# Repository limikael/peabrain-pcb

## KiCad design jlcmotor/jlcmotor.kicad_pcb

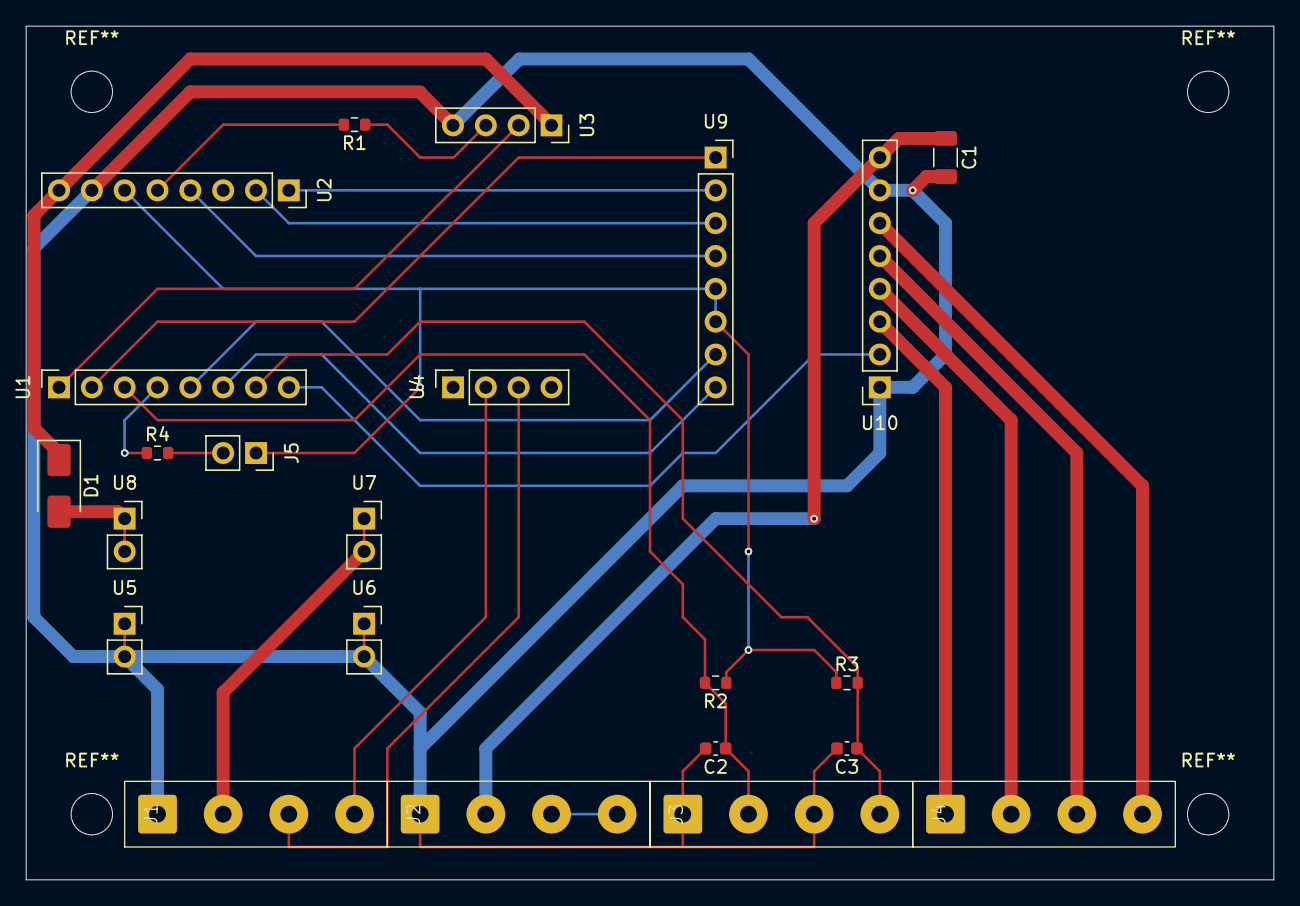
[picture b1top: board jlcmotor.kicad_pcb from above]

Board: 2 copper layers, 96.5 x 66.0 mm, 23 parts (0 on the bottom side), 26 nets.

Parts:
C1: C_1206_3216Metric
C2, C3: C_0603_1608Metric
D1: D_SMA
J1: ScrewTerminal; ScrewTerminals_4P
J2, J3, J4: ScrewTerminals_4P
J5: PinSocket_1x02_P2.54mm_Vertical
R1, R2, R3, R4: R_0603_1608Metric
U1, U2: PinHeader8; PinSocket_1x08_P2.54mm_Vertical
U3, U4: PinSocket_1x04_P2.54mm_Vertical
U5, U6, U7, U8: PinSocket_1x02_P2.54mm_Vertical
U9, U10: PinSocket_1x08_P2.54mm_Vertical

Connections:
/3V3: J5.1, R2.1, R3.1, U2.6, U9.5, U9.6
/5V: D1.1 (K), U2.8, U3.1
/12V: J1.2, U7.1, U7.2
/CANH: J1.3, U4.3
/CANL: J1.4, U4.2
/GND: C1.2, C2.2, C3.2, J1.1, J2.1, J3.1, J3.3, U2.7, U3.4, U5.1, U5.2, U6.1, U6.2, U10.1, U10.7
/VMOT: C1.1, J2.2, U10.8
unnamed: D1.2 (A), U8.1, U8.2
unnamed: C2.1, J3.2, R2.2, U1.3
unnamed: C3.1, J3.4, R3.2, U1.7
unnamed: J4.1, U10.3
unnamed: J4.2, U10.4
unnamed: J4.3, U10.5
unnamed: J4.4, U10.6
unnamed: J5.2, R4.2
unnamed: U1.1, U3.2
unnamed: U1.2, U9.1
unnamed: R4.1, U1.4
unnamed: U1.5, U9.7
unnamed: U1.6, U9.8
unnamed: U1.8, U10.2
unnamed: U2.1, U9.2
unnamed: U2.2, U9.3
unnamed: U2.4, U9.4
unnamed: R1.2, U2.5
unnamed: R1.1, U3.3

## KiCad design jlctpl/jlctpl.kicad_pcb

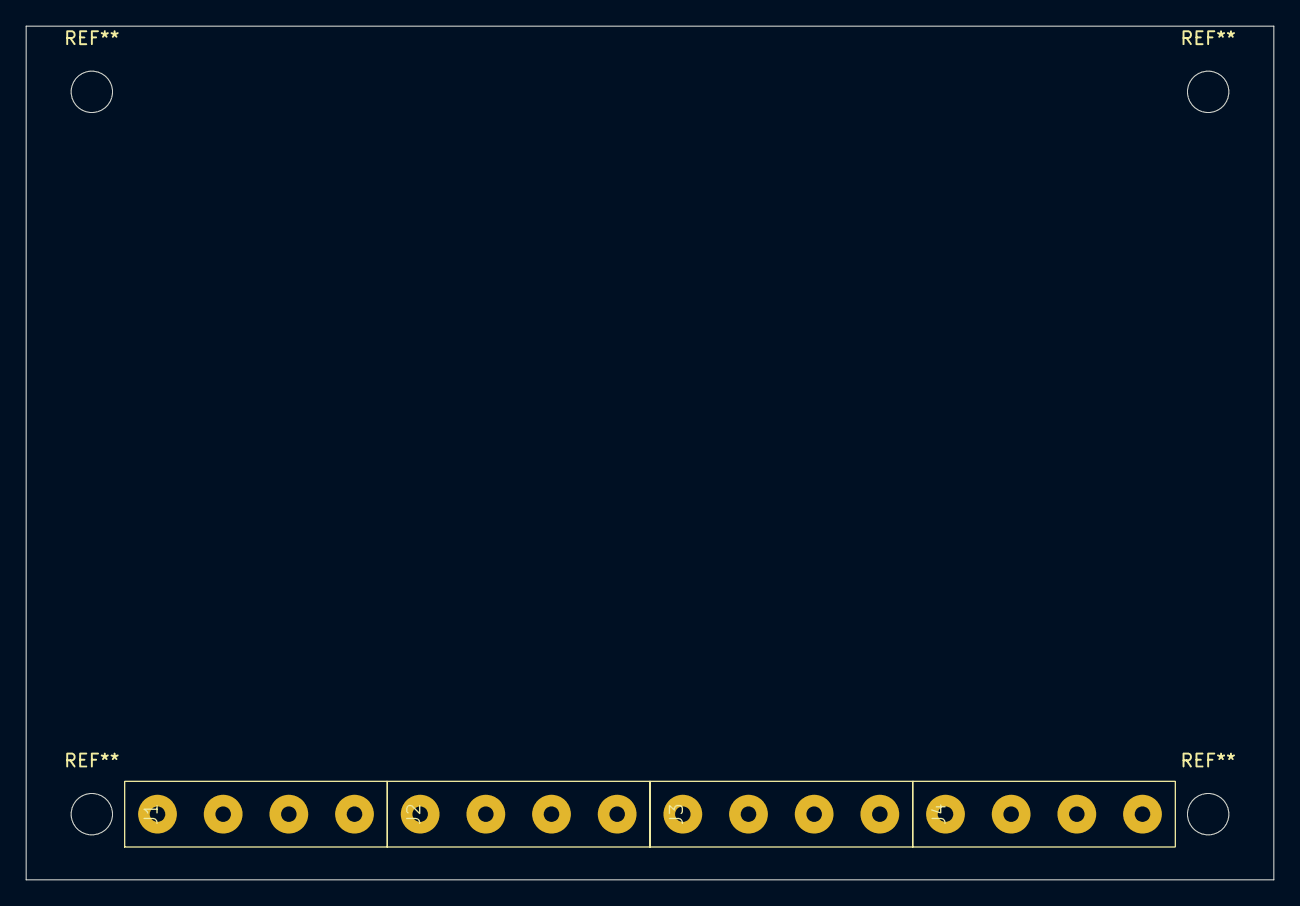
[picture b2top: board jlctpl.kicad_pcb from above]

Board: 2 copper layers, 96.5 x 66.0 mm, 4 parts (0 on the bottom side), 2 nets, no tracks yet.

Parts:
J1, J3, J4: Screw Termial; ScrewTerminals_4P
J2: Screw Terminal; ScrewTerminals_4P

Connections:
/3V3: J2.2, J3.2
/GND: J1.1, J2.1, J3.1

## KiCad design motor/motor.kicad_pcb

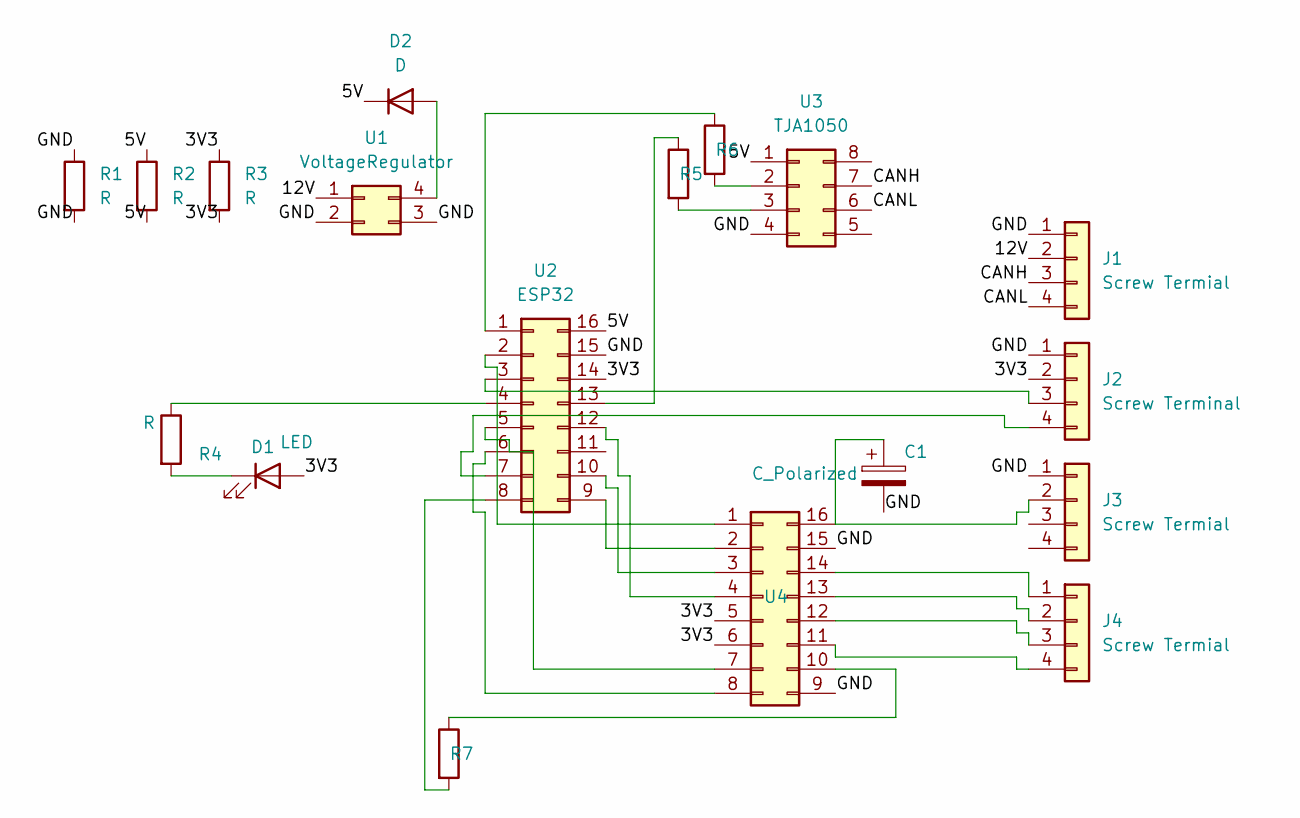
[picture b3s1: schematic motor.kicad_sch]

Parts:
C1: C_Polarized; PinHeader_1x02_P2.54mm_Vertical
D1: LED; PinHeader_Diode
D2: D; R_Axial_DIN0207_L6.3mm_D2.5mm_P10.16mm_Horizontal
J1, J3, J4: Screw Termial; ScrewTerminals_4P
J2: Screw Terminal; ScrewTerminals_4P
R1, R2, R3, R4: R; R_Axial_DIN0207_L6.3mm_D2.5mm_P10.16mm_Horizontal
R5, R6: R_Axial_DIN0207_L6.3mm_D2.5mm_P10.16mm_Horizontal
R7: R_Axial_DIN0207_L6.3mm_D2.5mm_P10.16mm_Horizontal
U1: VoltageRegulator
U2: ESP32
U3: TJA1050
U4: DRV8825

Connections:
/3V3: D1.2 (A), J2.2, R3.1, R3.2, U2.14, U4.5, U4.6
/5V: D2.1 (K), R2.1, R2.2, U2.16, U3.1
/12V: J1.2, U1.1
/CANH: J1.3, U3.7
/CANL: J1.4, U3.6
/GND: C1.2, J1.1, J2.1, J3.1, R1.1, R1.2, U1.2, U1.3, U2.15, U3.4, U4.9, U4.15
unnamed: D1.1 (K), R4.2
unnamed: D2.2 (A), U1.4
unnamed: J2.3, U2.3
unnamed: J2.4, U2.7
unnamed: C1.1, J3.2, U4.16
unnamed: J4.1, U4.14
unnamed: J4.2, U4.13
unnamed: J4.3, U4.12
unnamed: J4.4, U4.11
unnamed: R6.1, U2.1
unnamed: U2.2, U4.1
unnamed: R4.1, U2.4
unnamed: U2.5, U4.7
unnamed: U2.6, U4.8
unnamed: R7.2, U2.8
unnamed: U2.9, U4.2
unnamed: U2.10, U4.3
unnamed: U2.12, U4.4
unnamed: R5.1, U2.13
unnamed: R6.2, U3.2
unnamed: R5.2, U3.3
unnamed: R7.1, U4.10

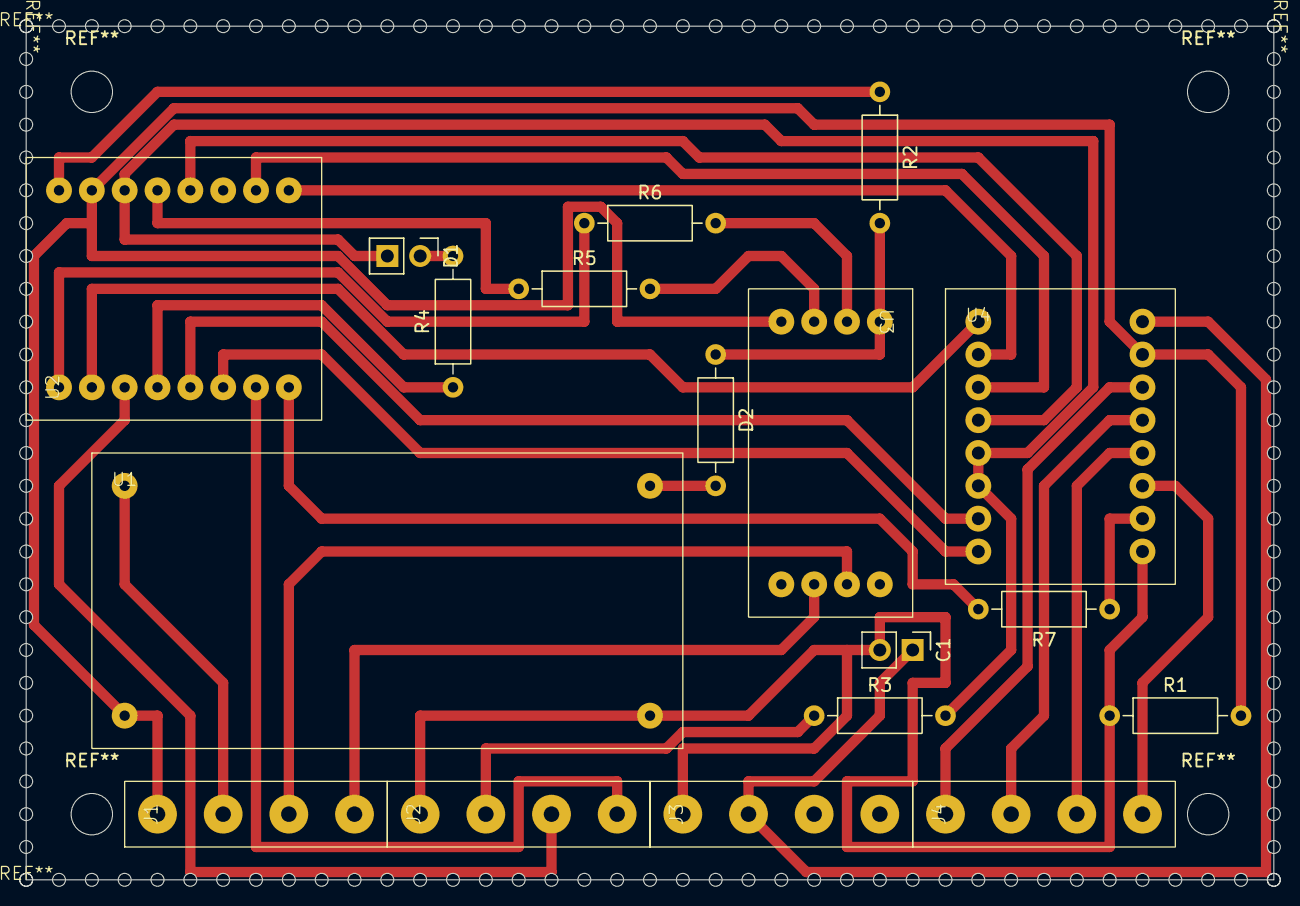
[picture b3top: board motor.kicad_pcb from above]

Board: 2 copper layers, 96.5 x 66.0 mm, 18 parts (0 on the bottom side), 28 nets.

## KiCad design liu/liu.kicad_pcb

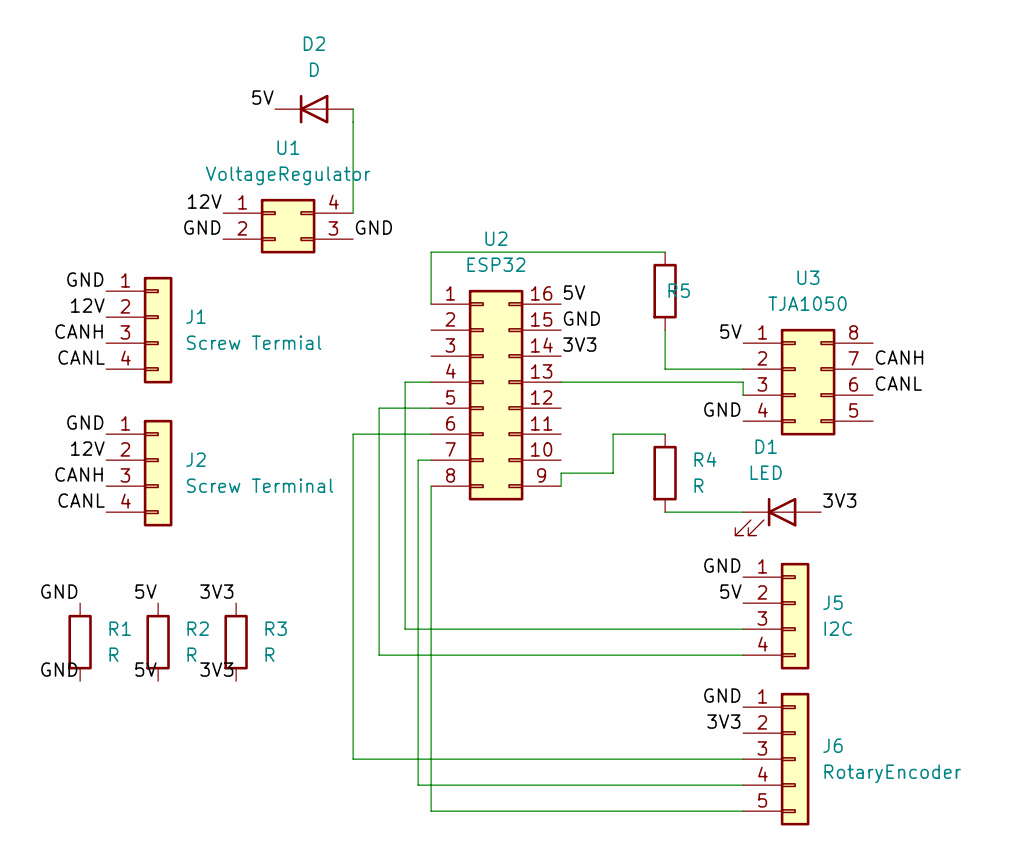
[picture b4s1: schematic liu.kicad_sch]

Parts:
D1: LED; PinHeader_1x02_P2.54mm_Vertical
D2: D; R_Axial_DIN0207_L6.3mm_D2.5mm_P10.16mm_Horizontal
J1: Screw Termial; ScrewTerminals_4P
J2: Screw Terminal; ScrewTerminals_4P
J5: I2C; I2C_Connector
J6: RotaryEncoder; RotaryEncoderConnection
R1, R2, R3, R4: R; R_Axial_DIN0207_L6.3mm_D2.5mm_P10.16mm_Horizontal
R5: R_Axial_DIN0207_L6.3mm_D2.5mm_P10.16mm_Horizontal
U1: VoltageRegulator
U2: ESP32
U3: TJA1050

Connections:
/3V3: D1.2 (A), J6.2, R3.1, R3.2, U2.14
/5V: D2.1 (K), J5.2, R2.1, R2.2, U2.16, U3.1
/12V: J1.2, J2.2, U1.1
/CANH: J1.3, J2.3, U3.7
/CANL: J1.4, J2.4, U3.6
/GND: J1.1, J2.1, J5.1, J6.1, R1.1, R1.2, U1.2, U1.3, U2.15, U3.4
unnamed: D1.1 (K), R4.2
unnamed: D2.2 (A), U1.4
unnamed: J5.3, U2.4
unnamed: J5.4, U2.5
unnamed: J6.3, U2.6
unnamed: J6.4, U2.7
unnamed: J6.5, U2.8
unnamed: R5.1, U2.1
unnamed: R4.1, U2.9
unnamed: U2.13, U3.3
unnamed: R5.2, U3.2

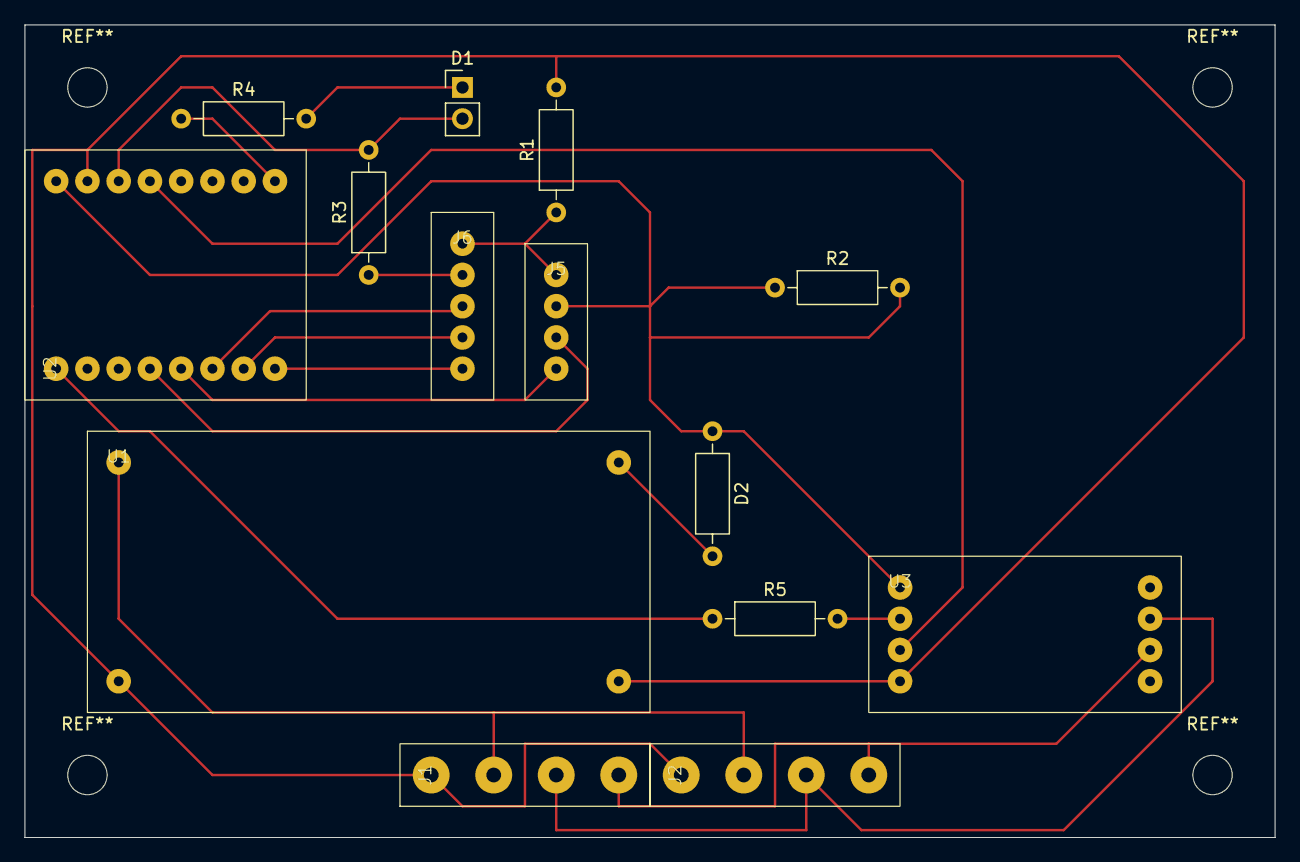
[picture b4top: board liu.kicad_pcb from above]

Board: 2 copper layers, 101.6 x 66.0 mm, 14 parts (0 on the bottom side), 17 nets.

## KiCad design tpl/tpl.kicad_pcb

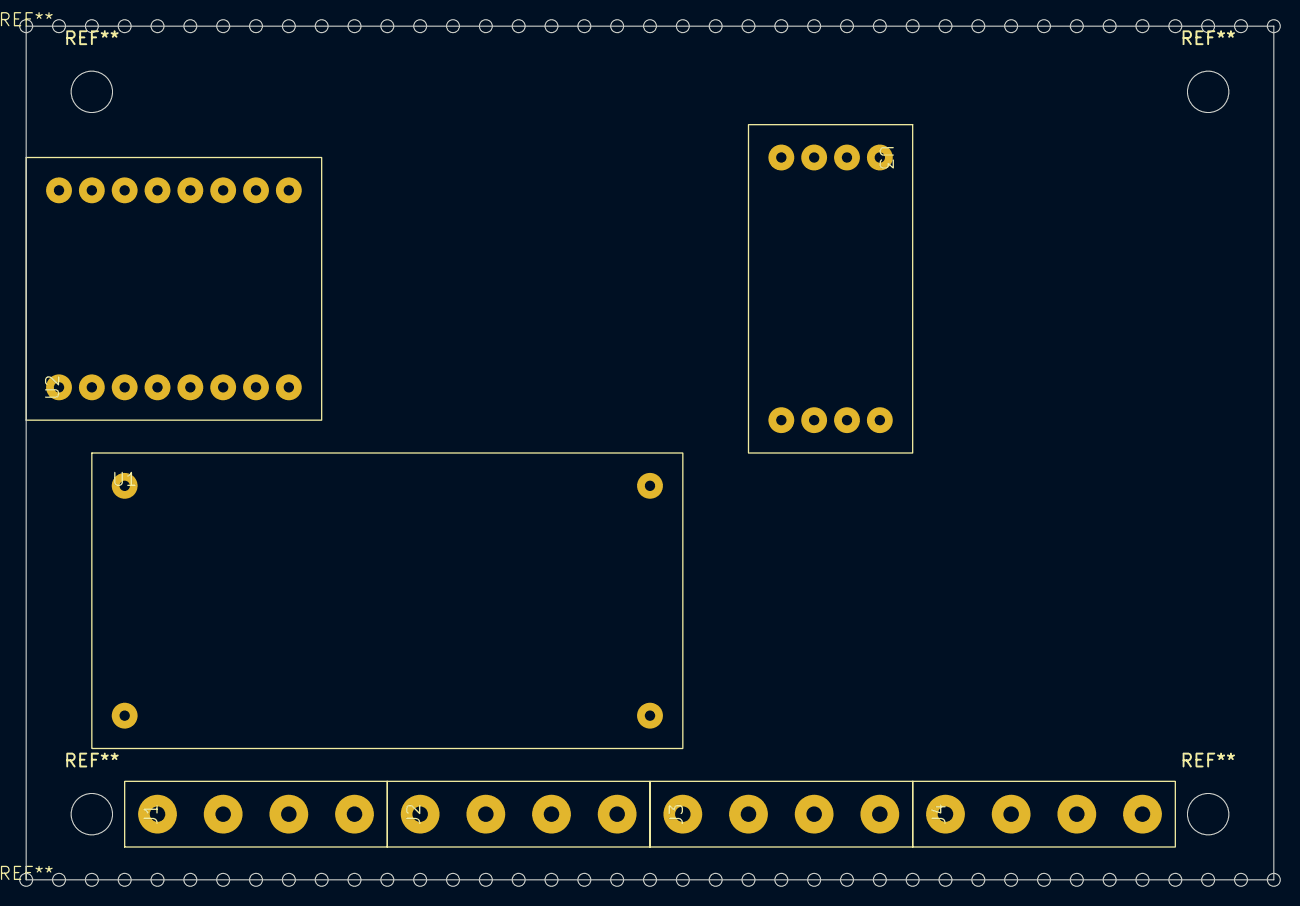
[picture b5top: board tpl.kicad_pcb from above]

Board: 2 copper layers, 96.5 x 66.0 mm, 7 parts (0 on the bottom side), 13 nets, no tracks yet.

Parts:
J1, J3, J4: Screw Termial; ScrewTerminals_4P
J2: Screw Terminal; ScrewTerminals_4P
U1: VoltageRegulator
U2: ESP32
U3: TJA1050

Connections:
/3V3: J2.2, J3.2, U2.14
/5V: U2.16, U3.1
/12V: J1.2, U1.1
/CANH: J1.3, U3.7
/CANL: J1.4, U3.6
/GND: J1.1, J2.1, J3.1, U1.2, U1.3, U2.15, U3.4
unnamed: J2.3, U2.9
unnamed: J2.4, U2.10
unnamed: J3.4, U2.2
unnamed: J4.1, U2.3
unnamed: J4.2, U2.6
unnamed: J4.3, U2.7
unnamed: J4.4, U2.8

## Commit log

2026-02-18 added stuff
2026-02-21 script update
2026-02-26 4 screw terminals
2026-03-08 gpio
2026-03-25 stuff
2026-03-28 kisch and jlcc
2026-03-28 bulk capacitor
2026-03-28 limit sw
2026-03-28 status led and power oring
2026-05-16 new kisch
